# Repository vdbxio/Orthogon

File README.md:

# Orthogon

**What is Orthogon?**

Orthogon is an acrylic edge-lit name badge. Our goals for Orthogon are beauty, simplicity, and accessibility to hobbyists.

Orthogon is composed of just a few pieces, including:

* An acrylic body through which light shines. The first iteration is designed around 1/4ish" acrylic (5.6 ~ 6 mm thick)
* A simple driver board which includes 4 SK6812 Mini LEDs (Mini Neopixels) and an ATtiny85 to drive them
* A means of clipping Orthogon to your clothing and connecting to the battery system
* A battery system that includes a LiPo cell, charge/protect/boost (CPB) circuitry, and a mating clip to attach to the visible portion of Orthogon

***

Project status:

Designed and testing:
* Acrylic body
* LED/driver board

Next up
* Battery system
* Clip system

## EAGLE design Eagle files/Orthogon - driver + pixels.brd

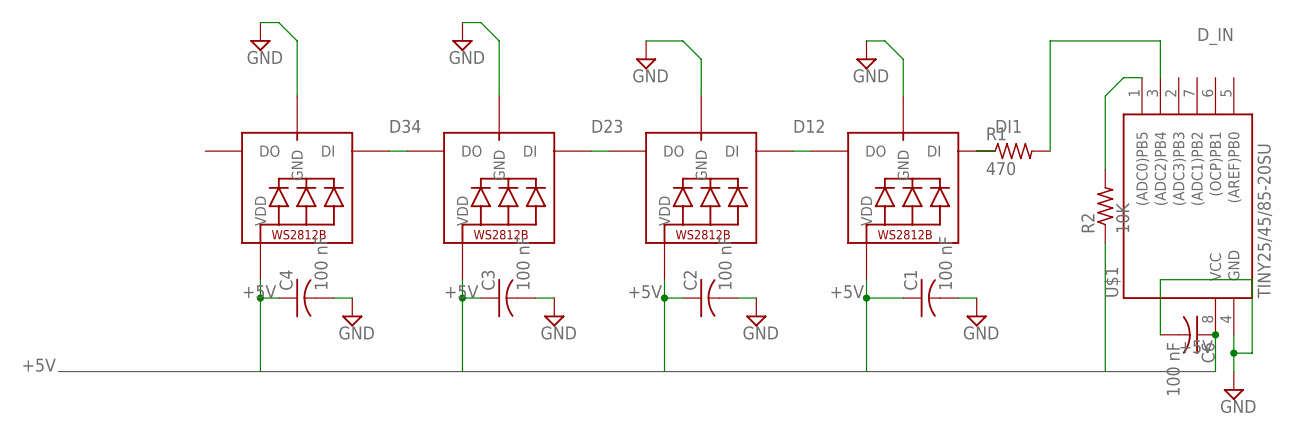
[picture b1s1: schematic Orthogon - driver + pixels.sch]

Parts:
C1, C2, C3, C4, C6: 100 nF; C0402
LED2, LED3, LED4, LED5: WS2812B3535; LED3535
R1: 470; R0402
R2: 10K; R0402
U$1: TINY25/45/85-20SU; SOIC8

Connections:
+5V: C1.1, C2.1, C3.1, C4.1, C6.1, LED2.2 (VDD), LED3.2 (VDD), LED4.2 (VDD), LED5.2 (VDD), R2.1, R2.2, U$1.1 ((ADC0)PB5), U$1.8 (VCC)
D12: LED4.1 (DI), LED5.3 (DO)
D23: LED3.1 (DI), LED4.3 (DO)
D34: LED2.1 (DI), LED3.3 (DO)
DI1: LED5.1 (DI), R1.1
D_IN: R1.2, U$1.3 ((ADC2)PB4)
GND: C1.2, C2.2, C3.2, C4.2, C6.2, LED2.4 (GND), LED3.4 (GND), LED4.4 (GND), LED5.4 (GND), U$1.4 (GND)

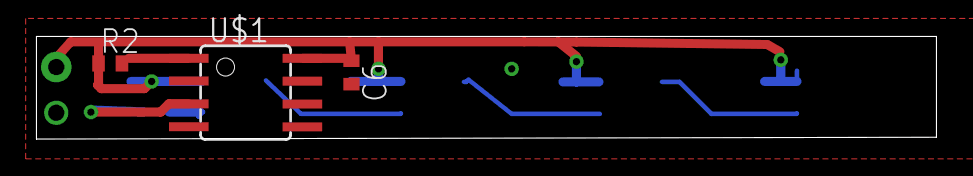
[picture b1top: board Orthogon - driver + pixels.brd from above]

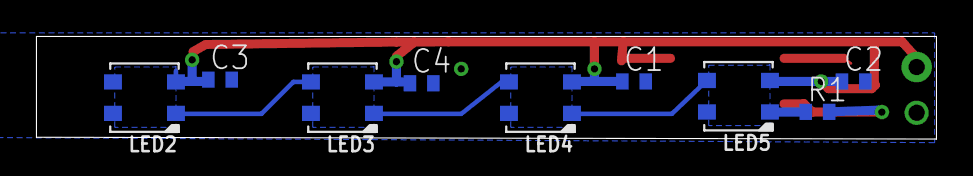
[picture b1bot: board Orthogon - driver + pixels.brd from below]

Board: 2 copper layers, 50.0 x 5.7 mm, 12 parts (9 on the bottom side), 7 nets.

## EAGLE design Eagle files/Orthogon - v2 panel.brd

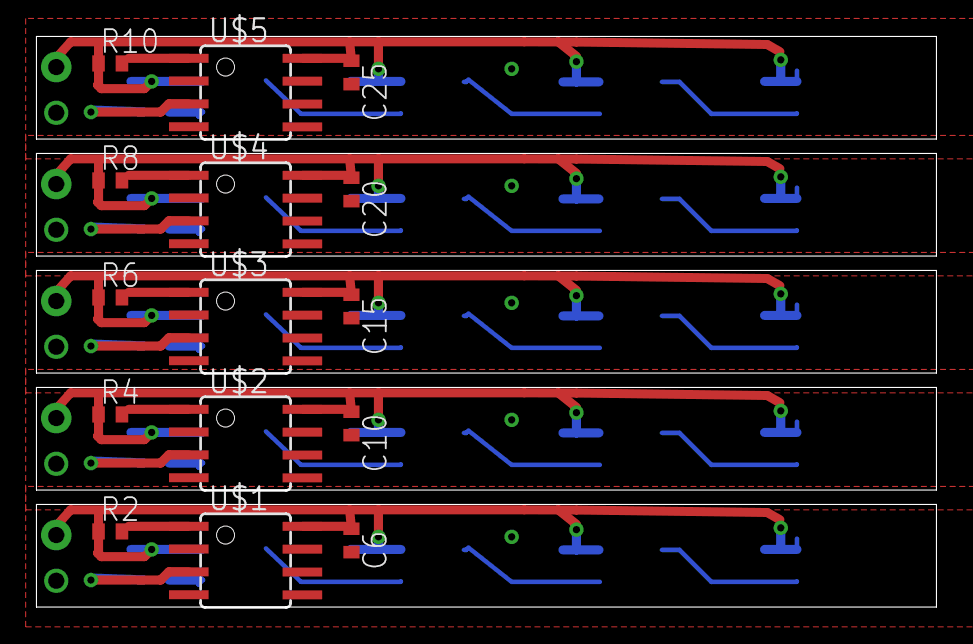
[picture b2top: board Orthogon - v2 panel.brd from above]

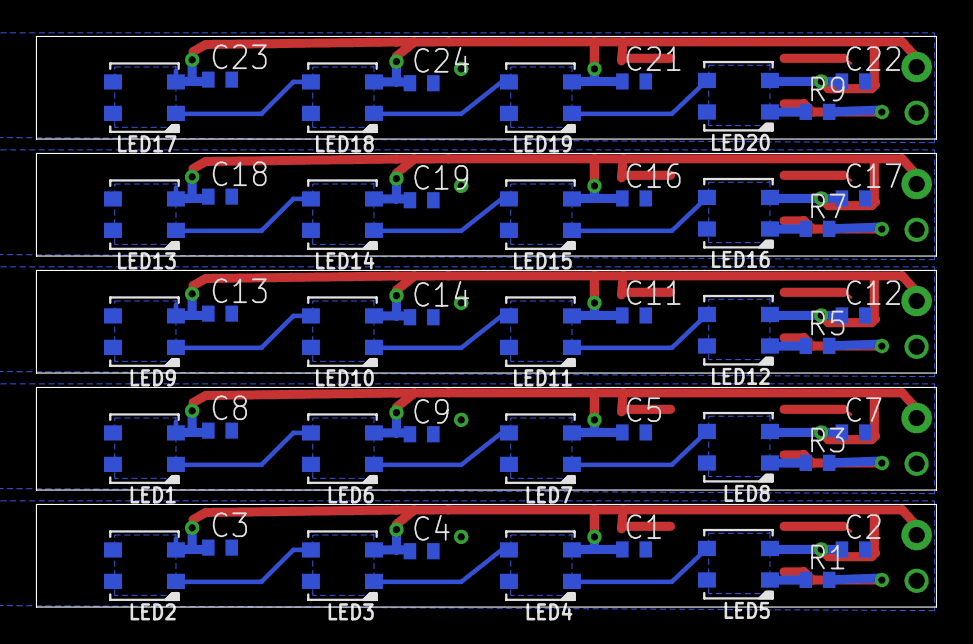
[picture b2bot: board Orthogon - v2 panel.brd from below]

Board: 2 copper layers, 50.0 x 31.7 mm, 60 parts (45 on the bottom side), 35 nets.

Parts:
C1, C2, C3, C4, C5, C6, C7, C8, C9, C10, C11, C12, C13, C14, C15, C16, C17, C18, C19, C20, C21, C22, C23, C24, C25: 100 nF; C0402
LED1, LED2, LED3, LED4, LED5, LED6, LED7, LED8, LED9, LED10, LED11, LED12, LED13, LED14, LED15, LED16, LED17, LED18, LED19, LED20: WS2812B3535; LED3535
R1, R3, R5, R7, R9: 470; R0402
R2, R4, R6, R8, R10: 10K; R0402
U$1, U$2, U$3, U$4, U$5: TINY25/45/85-20SU; SOIC8

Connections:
+5V: C1.1, C2.1, C3.1, C4.1, C6.1, LED2.2, LED3.2, LED4.2, LED5.2, R2.1, R2.2, U$1.1, U$1.8
+5V1: C5.1, C7.1, C8.1, C9.1, C10.1, LED1.2, LED6.2, LED7.2, LED8.2, R4.1, R4.2, U$2.1, U$2.8
+5V2: C11.1, C12.1, C13.1, C14.1, C15.1, LED9.2, LED10.2, LED11.2, LED12.2, R6.1, R6.2, U$3.1, U$3.8
+5V3: C16.1, C17.1, C18.1, C19.1, C20.1, LED13.2, LED14.2, LED15.2, LED16.2, R8.1, R8.2, U$4.1, U$4.8
+5V4: C21.1, C22.1, C23.1, C24.1, C25.1, LED17.2, LED18.2, LED19.2, LED20.2, R10.1, R10.2, U$5.1, U$5.8
D1: LED7.1, LED8.3
D2: LED6.1, LED7.3
D3: LED1.1, LED6.3
D4: LED11.1, LED12.3
D5: LED10.1, LED11.3
D6: LED9.1, LED10.3
D7: LED15.1, LED16.3
D8: LED14.1, LED15.3
D9: LED13.1, LED14.3
D10: LED19.1, LED20.3
D11: LED18.1, LED19.3
D12: LED4.1, LED5.3
D13: LED17.1, LED18.3
D23: LED3.1, LED4.3
D34: LED2.1, LED3.3
DI1: LED5.1, R1.1
DI2: LED8.1, R3.1
DI3: LED12.1, R5.1
DI4: LED16.1, R7.1
DI5: LED20.1, R9.1
D_IN: R1.2, U$1.3
D_IN1: R3.2, U$2.3
D_IN2: R5.2, U$3.3
D_IN3: R7.2, U$4.3
D_IN4: R9.2, U$5.3
GND: C1.2, C2.2, C3.2, C4.2, C6.2, LED2.4, LED3.4, LED4.4, LED5.4, U$1.4
GND1: C5.2, C7.2, C8.2, C9.2, C10.2, LED1.4, LED6.4, LED7.4, LED8.4, U$2.4
GND2: C11.2, C12.2, C13.2, C14.2, C15.2, LED9.4, LED10.4, LED11.4, LED12.4, U$3.4
GND3: C16.2, C17.2, C18.2, C19.2, C20.2, LED13.4, LED14.4, LED15.4, LED16.4, U$4.4
GND4: C21.2, C22.2, C23.2, C24.2, C25.2, LED17.4, LED18.4, LED19.4, LED20.4, U$5.4

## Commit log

2018-08-24 Eagle upload
    Initial upload of Eagle files. Board file for single Orthogon board and 1x5 panel.
    Also includes gcode file for milling a stencil for the 1x5 array
2018-08-24 Revert "Eagle upload"
    This reverts commit 1e5974ec236e374d1687608480889fea6aaf0027.
2018-08-24 Upload Eagle files for LED board
    Upload LED Board, 1x5 array, and stencil
2018-08-24 First Fusion360 upload
    Added rough Fusion360 mockup of acrylic body and LED board
